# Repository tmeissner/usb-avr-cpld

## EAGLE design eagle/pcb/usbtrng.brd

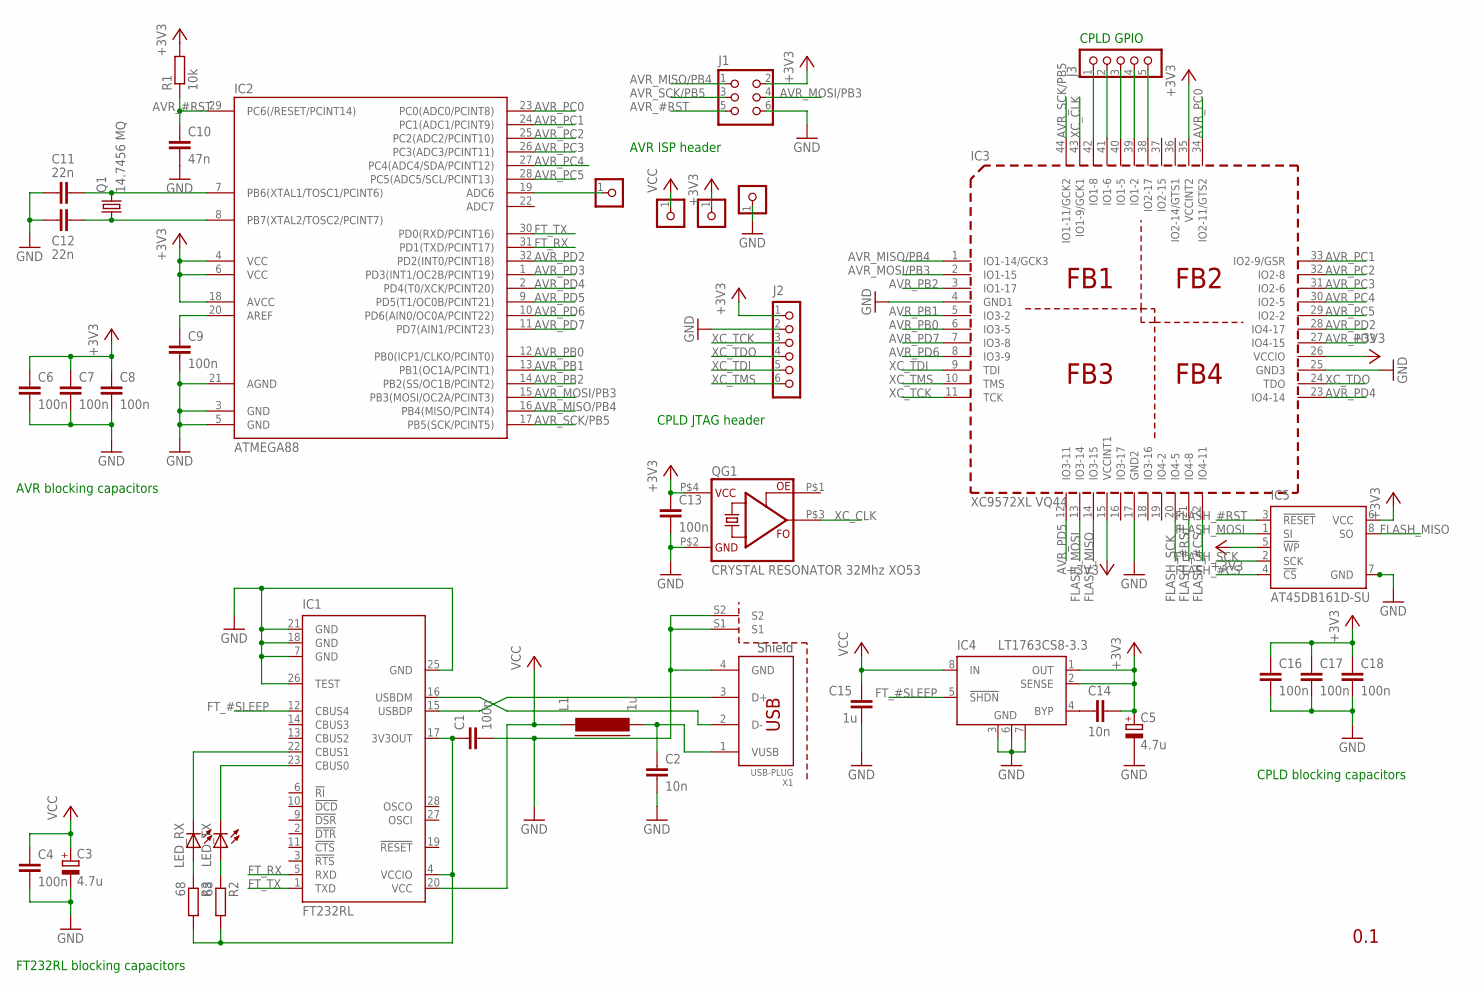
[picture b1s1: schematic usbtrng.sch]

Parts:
C1, C4, C6, C7, C8, C9, C13, C16, C17, C18: 100n; C0805
C2, C14: 10n; C0805
C3, C5: 4.7u; PANASONIC_B
C10: 47n; C0805
C11, C12: 22n; C0805
C15: 1u; C0805
IC1: FT232RL; SSOP28
IC2: ATMEGA88; TQFP32-08
IC3: XC9572XL VQ44; VQ-44
IC4: LT1763CS8-3.3; SOIC8
IC5: AT45DB161D-SU; 8S2
J1: CON_HEADER_2X03-PTH; M2X3
J2: CON_HEADER_1X06-PTH; M1X6
J3: CON_HEADER_1X05-PTH; M1X5
J4, J5, J7, J8: CON_HEADER_1X01-PTH; M1X1
L1: 1u; FB805
LED_RX: LEDCHIP-LED0805; CHIP-LED0805
LED_TX: LEDCHIP-LED0805; CHIP-LED0805
Q1: 14.7456 MQ; MJ
QG1: CRYSTAL RESONATOR 32Mhz XO53; XO53
R1: 10k; M0805
R2, R3: 68; M0805
X1: USB-PLUG; USB-PLUG-A-SMD-2S

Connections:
+3V3: C5.+, C6.1, C7.1, C8.1, C13.1, C14.2, C16.1, C17.1, C18.1, IC2.4 (VCC), IC2.6 (VCC), IC2.18 (AVCC), IC3.15 (VCCINT1), IC3.26 (VCCIO), IC3.35 (VCCINT2), IC4.1 (OUT), IC4.2 (SENSE), IC5.5 (!WP), IC5.6 (VCC), J1.2, J2.1, J7.1, QG1.P$4 (VCC), R1.2
AVR_#RST: C10.1, IC2.29 (PC6(/RESET/PCINT14)), J1.5, R1.1
AVR_MISO/PB4: IC2.16 (PB4(MISO/PCINT4)), IC3.1 (IO1-14/GCK3), J1.1
AVR_MOSI/PB3: IC2.15 (PB3(MOSI/OC2A/PCINT3)), IC3.2 (IO1-15), J1.4
AVR_PB0: IC2.12 (PB0(ICP1/CLKO/PCINT0)), IC3.6 (IO3-5)
AVR_PB1: IC2.13 (PB1(OC1A/PCINT1)), IC3.5 (IO3-2)
AVR_PB2: IC2.14 (PB2(SS/OC1B/PCINT2)), IC3.3 (IO1-17)
AVR_PC0: IC2.23 (PC0(ADC0/PCINT8)), IC3.34 (IO2-11/GTS2)
AVR_PC1: IC2.24 (PC1(ADC1/PCINT9)), IC3.33 (IO2-9/GSR)
AVR_PC2: IC2.25 (PC2(ADC2/PCINT10)), IC3.32 (IO2-8)
AVR_PC3: IC2.26 (PC3(ADC3/PCINT11)), IC3.31 (IO2-6)
AVR_PC4: IC2.27 (PC4(ADC4/SDA/PCINT12)), IC3.30 (IO2-5)
AVR_PC5: IC2.28 (PC5(ADC5/SCL/PCINT13)), IC3.29 (IO2-2)
AVR_PD2: IC2.32 (PD2(INT0/PCINT18)), IC3.28 (IO4-17)
AVR_PD3: IC2.1 (PD3(INT1/OC2B/PCINT19)), IC3.27 (IO4-15)
AVR_PD4: IC2.2 (PD4(T0/XCK/PCINT20)), IC3.23 (IO4-14)
AVR_PD5: IC2.9 (PD5(T1/OC0B/PCINT21)), IC3.12 (IO3-11)
AVR_PD6: IC2.10 (PD6(AIN0/OC0A/PCINT22)), IC3.8 (IO3-9)
AVR_PD7: IC2.11 (PD7(AIN1/PCINT23)), IC3.7 (IO3-8)
AVR_SCK/PB5: IC2.17 (PB5(SCK/PCINT5)), IC3.44 (IO1-11/GCK2), J1.3
FLASH_#CS: IC3.22 (IO4-11), IC5.4 (!CS)
FLASH_#RST: IC3.21 (IO4-8), IC5.3 (!RESET)
FLASH_MISO: IC3.14 (IO3-15), IC5.8 (SO)
FLASH_MOSI: IC3.13 (IO3-14), IC5.1 (SI)
FLASH_SCK: IC3.20 (IO4-5), IC5.2 (SCK)
FT_#SLEEP: IC1.12 (CBUS4), IC4.5 (!SHDN)
FT_RX: IC1.5 (RXD), IC2.31 (PD1(TXD/PCINT17))
FT_TX: IC1.1 (TXD), IC2.30 (PD0(RXD/PCINT16))
GND: C1.2, C2.2, C3.-, C4.2, C5.-, C6.2, C7.2, C8.2, C9.2, C10.2, C11.1, C12.1, C13.2, C15.1, C16.2, C17.2, C18.2, IC1.7 (GND), IC1.18 (GND), IC1.21 (GND), IC1.25 (GND), IC1.26 (TEST), IC2.3 (GND), IC2.5 (GND), IC2.21 (AGND), IC3.4 (GND1), IC3.17 (GND2), IC3.25 (GND3), IC4.3 (GND), IC4.6 (GND), IC4.7 (GND), IC5.7 (GND), J1.6, J2.2, J5.1, QG1.P$2 (GND), X1.4 (GND), X1.S1, X1.S2
unnamed: IC1.15 (USBDP), X1.3 (D+)
unnamed: IC1.16 (USBDM), X1.2 (D-)
unnamed: C9.1, IC2.20 (AREF)
unnamed: C2.1, L1.2, X1.1 (VUSB)
unnamed: LED_RX.A, R3.1
unnamed: C1.1, IC1.4 (VCCIO), IC1.17 (3V3OUT), R2.2, R3.2
unnamed: LED_TX.A, R2.1
unnamed: IC1.23 (CBUS0), LED_TX.C
unnamed: IC1.22 (CBUS1), LED_RX.C
unnamed: C11.2, IC2.7 (PB6(XTAL1/TOSC1/PCINT6)), Q1.P3 (2)
unnamed: C12.2, IC2.8 (PB7(XTAL2/TOSC2/PCINT7)), Q1.P1 (1)
unnamed: IC3.42 (IO1-8), J3.1
unnamed: C14.1, IC4.4 (BYP)
unnamed: IC3.41 (IO1-6), J3.2
unnamed: IC3.40 (IO1-5), J3.3
unnamed: IC3.39 (IO1-2), J3.4
unnamed: IC3.38 (IO2-17), J3.5
unnamed: IC2.19 (ADC6), J4.1
VCC: C3.+, C4.1, C15.2, IC1.20 (VCC), IC4.8 (IN), J8.1, L1.1
XC_CLK: IC3.43 (IO1-9/GCK1), QG1.P$3 (FO)
XC_TCK: IC3.11 (TCK), J2.3
XC_TDI: IC3.9 (TDI), J2.5
XC_TDO: IC3.24 (TDO), J2.4
XC_TMS: IC3.10 (TMS), J2.6

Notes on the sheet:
FT232RL blocking capacitors
AVR blocking capacitors
CPLD blocking capacitors
AVR ISP header
CPLD JTAG header
0.1
CPLD GPIO

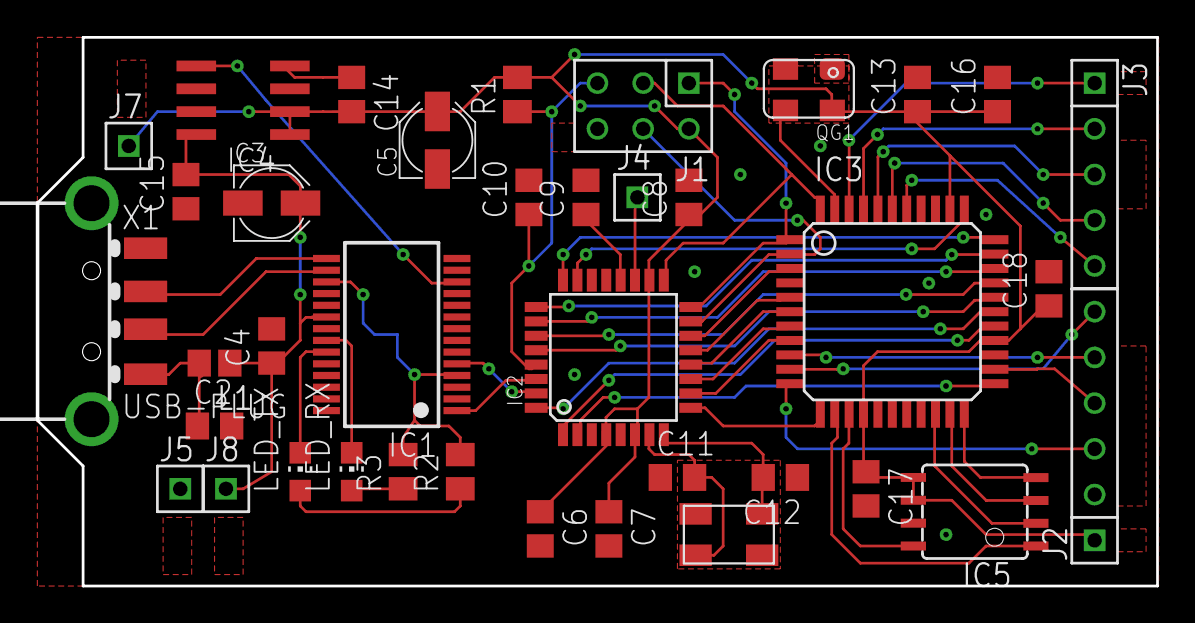
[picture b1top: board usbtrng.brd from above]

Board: 4 copper layers, 62.2 x 30.5 mm, 39 parts (1 on the bottom side), 53 nets.

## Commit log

2012-09-12 initial commit of eagle files with additional data
    * design rules
    * libraries
    * schematic
    * board
2012-09-12 pics folder with some pictures & fotos of the project
2012-09-12 added schematic picture
2012-09-13 major revision of board layout
    * better signal routing around ft232rl
    * better placement of blockng capacitors
2012-09-13 version 0.1: update to major revision of layout
2012-09-13 This is the revision, that is manufactured at q-print, v.0.1
    * integrated 32 Mbit SPI-Flash, connected to the CPLD
    * The rx/tx leds are now powerd by VCCIO
    * further layout optimisations
2012-09-13 update to latest schematic & board revision, now version 0.1 which is manufactured at q-print :)
2012-09-13 initial commit of design rules for manufacturing the pcb at q-print
2012-09-26 new folder 'avr' with test project to test the AVR on USB-AVR-CPLD
    * makefile with compile, program & clean targets
    * src/avrtest.c file with test code (@ the moment a simple uart loop)
2012-09-26 initial commit of the project README file
    * added short description
    * a nice photo to see, what's all about
2012-09-26 added closing of the image tag
2012-09-26 added link to the avr folder
2012-09-27 new folder 'cpld' with test project to test the CPLD on USB-AVR-CPLD
    * sim/makefile with targets to simulate the cpld design
    * sim/cpldtestt.vhd file with the testbench
    * sim/cpldtestt.tcl file with control commands for gtkwave
    * src/cpldteste.vhd file with test design (@ the moment a simple 10101 @ gpio port)
    * syn/constraints/cpldtest.ucf with implementation constraints
    * syn/makefile with targets to build the cpld design
2012-09-27 added description of the 'cpld' which contains the cpld test design
2012-09-27 initial commit of config folder & makefile for implementation
2012-09-27 bugfix: added 'NET' before the pin names
2012-09-27 wrapped gpio pin test code with a a synchronious process, sensitive to XcClk_i
2012-09-27 change timespec name from TS_Clk_i to TS_XcClk_i
2012-10-10 declaration of F_CPU now in the makefile, only check in the c-source, if it was forgotten
2012-12-08 added gpl-v2 license text

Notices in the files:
eagle/pcb/usbtrng.brd:
(c) 2012 by T. Meissner - www.github.com/tmeissner
